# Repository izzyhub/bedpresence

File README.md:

# bedpresence

Wooohooo a new package!

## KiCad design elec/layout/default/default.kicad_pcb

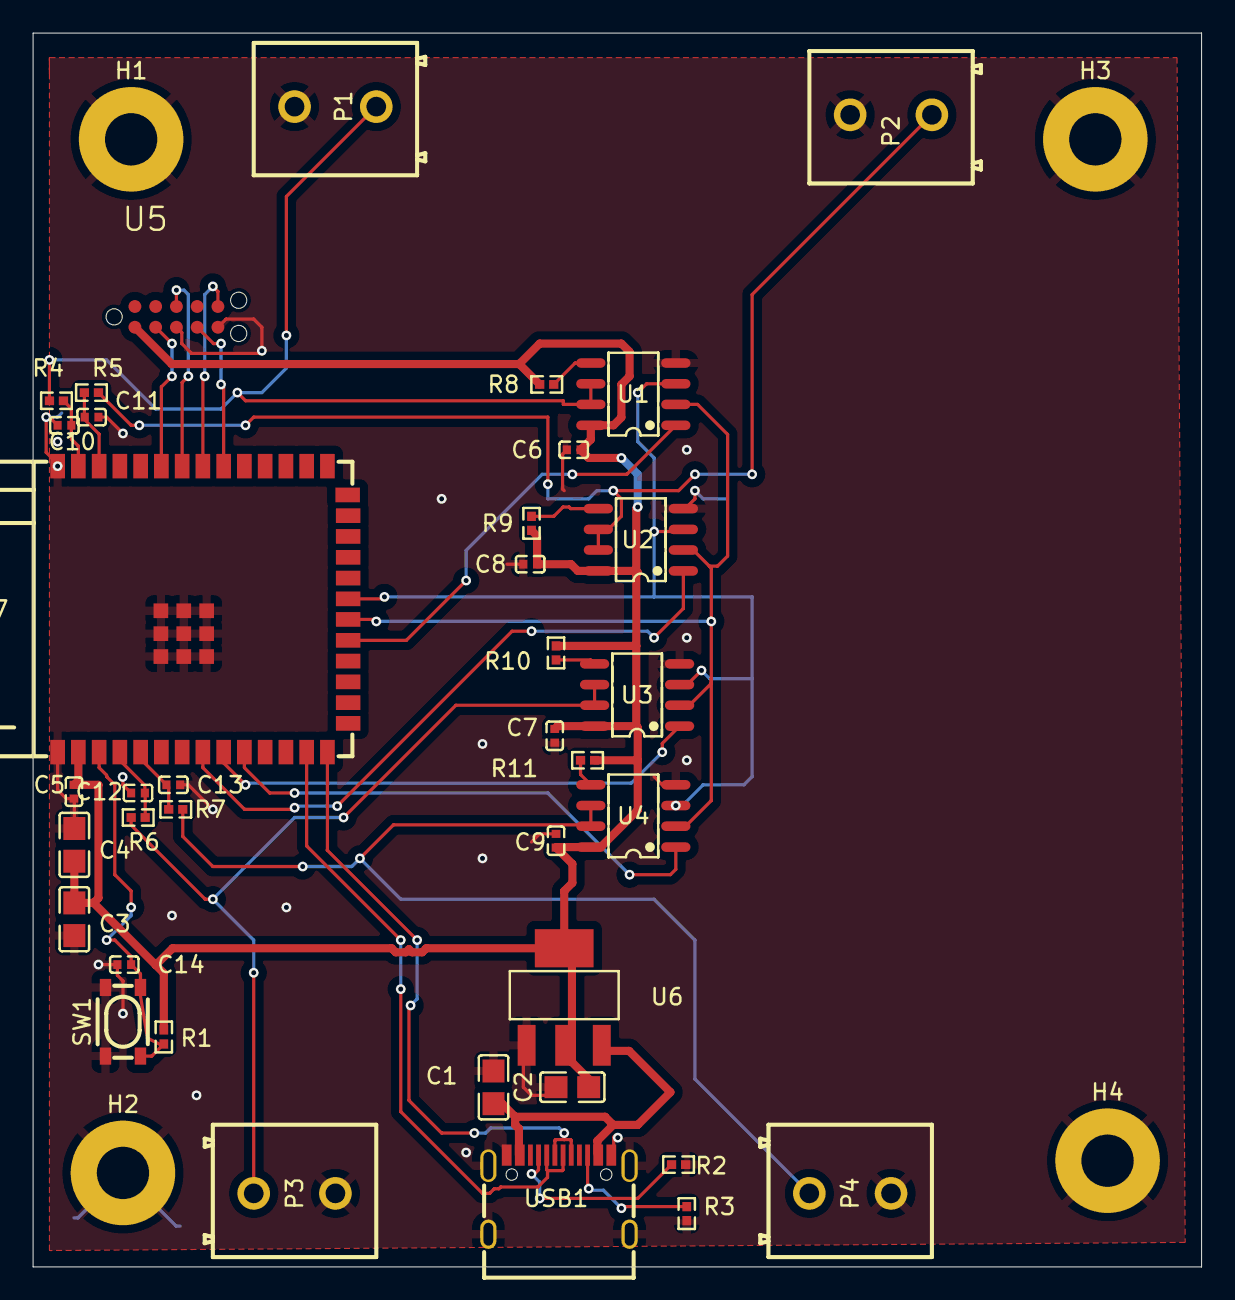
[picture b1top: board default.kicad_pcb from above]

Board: 2 copper layers, 71.5 x 75.5 mm, 42 parts (0 on the bottom side), 30 nets.

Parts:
C1, C3, C4: 10µF ±10%; C0805
C2: 22µF ±20%; C0805
C5, C6, C7, C8, C9, C10, C11, C12, C13: 100nF ±10%; C0402
C14: 1µF ±10%; C0402
H1, H2, H3, H4: MountingHole_3.2_M3_Pad
P1, P2, P3, P4: CONN-TH_2P-P5.00_CPC3703CTR
R1: 10kΩ ±1%; R0402
R2, R3: 5.1kΩ ±1%; R0402
R4, R5, R6, R7: 1kΩ ±1%; R0402
R8, R9, R10, R11: 4.02kΩ ±1%; R0402
SW1: KEY-SMD_4P-L4.2-W3.2-P2.20-LS4.6
U1, U2, U3, U4: SOIC-8_L4.9-W3.9-P1.27-LS6.0-BL
U5: TAG-CONNECT_TC2050-IDC
U6: SOT-223-3_L6.5-W3.4-P2.30-LS7.0-BR
U7: WIRELM-SMD_ESP32-S3-WROOM-1
USB1: USB-C-SMD_KH-TYPE-C-16P

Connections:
1: P1.1, R4.1, U1.6, U1.7
1-1: P2.1, R5.1, U2.6, U2.7
1-2: P3.1, R6.1, U3.6, U3.7
1-3: P4.1, R7.1, U4.6, U4.7
5: R8.2, U1.5
5-1: R9.2, U2.5
5-2: R10.2, U3.5
5-3: R11.2, U4.5
A5: R2.1, USB1.A5
B5: R3.1, USB1.B5
SI: U1.3, U2.3, U3.3, U4.3, U7.21
cs: U1.1, U7.19
digi_pot2-spi-cs: U2.1, U7.8
digi_pot3-spi-cs: U3.1, U7.9
digi_pot4-spi-cs: U4.1, U7.10
dm: U7.13, USB1.A7, USB1.B7
dp: U7.14, USB1.A6, USB1.B6
en_cap-power-hv: C14.1, R1.2, SW1.1, SW1.2, U7.3
filter_cap1-power-hv: C10.1, R4.2, U7.39
filter_cap2-power-hv: C11.1, R5.2, U7.38
filter_cap3-power-hv: C12.1, R6.2, U7.4
filter_cap4-power-hv: C13.1, R7.2, U7.5
hv: C2.1, C3.1, C4.1, C5.1, C6.1, C7.1, C8.1, C9.1, R1.1, R8.1, R9.1, R10.1, R11.1, U1.8, U2.8, U3.8, U4.8, U5.1, U6.2, U6.4, U7.2
input_cap-power-hv: C1.1, U6.3, USB1.A4, USB1.A9, USB1.B4, USB1.B9
lv: C1.2, C2.2, C3.2, C4.2, C5.2, C6.2, C7.2, C8.2, C9.2, C10.2, C11.2, C12.2, C13.2, C14.2, H1.1, H2.1, H3.1, H4.1, P1.2, P2.2, P3.2, P4.2, R2.2, R3.2, SW1.3, SW1.4, U1.4, U2.4, U3.4, U4.4, U5.3, U5.5, U6.1, U7.1, U7.40, U7.41, USB1.1, USB1.2, USB1.3, USB1.4, USB1.A1, USB1.A12, USB1.B1, USB1.B12
sck: U1.2, U2.2, U3.2, U4.2, U7.20
tck: U5.4, U7.32
tdi: U5.8, U7.34
tdo: U5.6, U7.33
tms: U5.2, U7.35

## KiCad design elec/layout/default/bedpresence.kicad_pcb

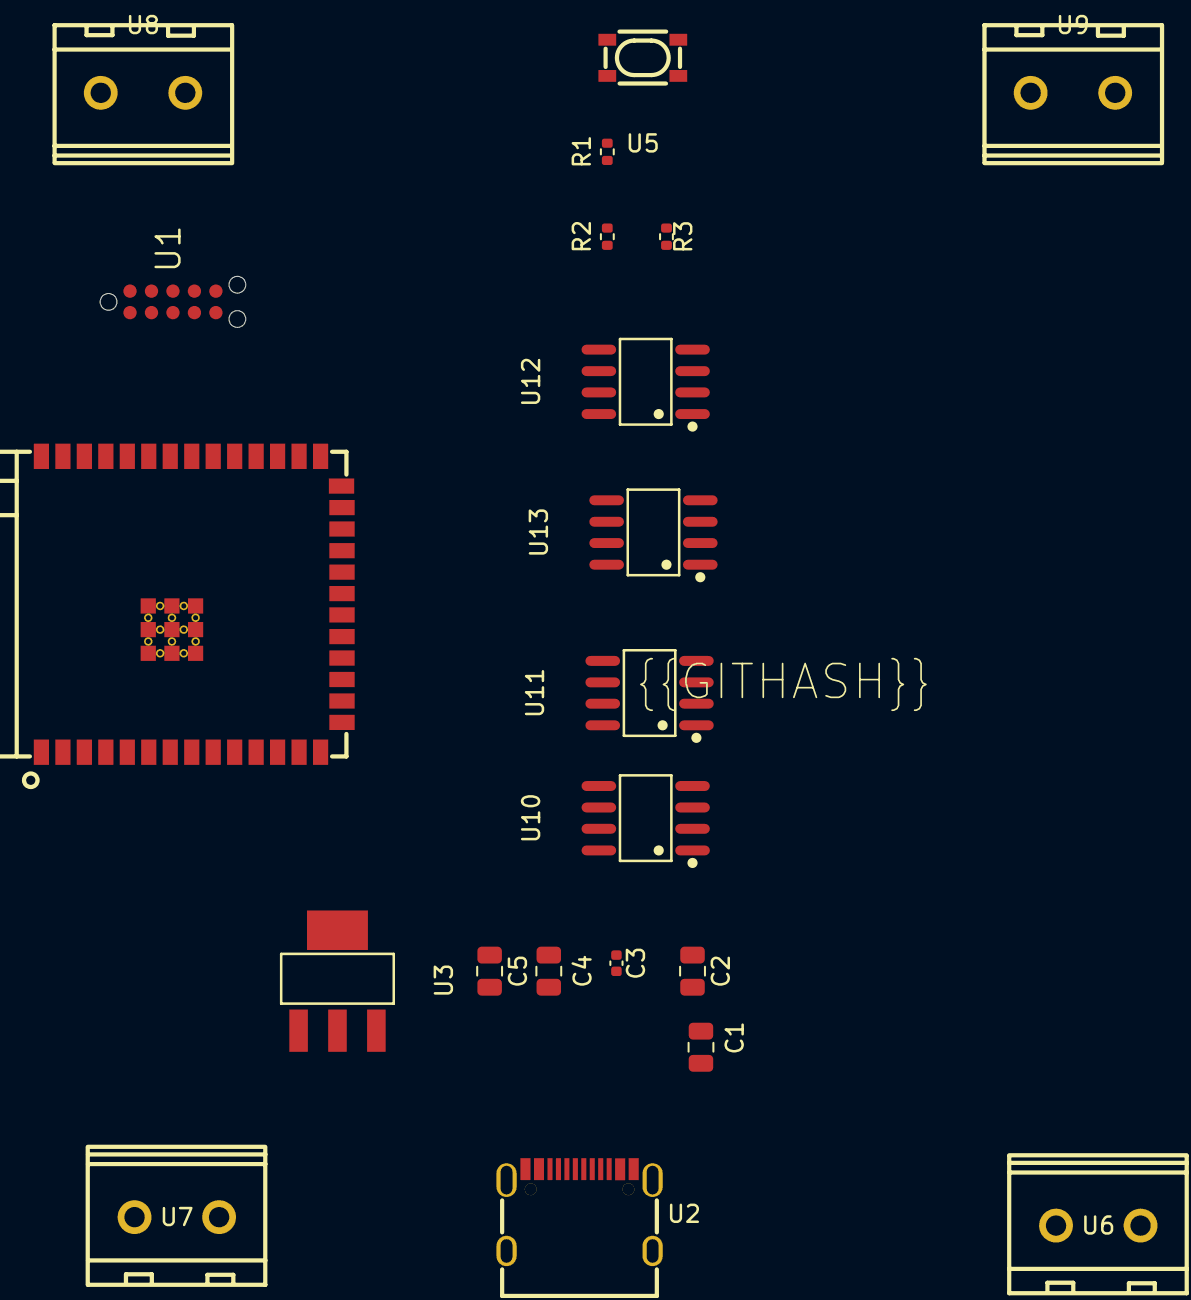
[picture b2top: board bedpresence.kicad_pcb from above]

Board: 2 copper layers, 21 parts (0 on the bottom side), 22 nets, no tracks yet.

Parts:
C1, C2, C4, C5: 25V 10uF X5R ±10% 0805 Multilayer Ceramic Capacit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; C0805
C3: 16V 100nF X7R ±10% 0402 Multilayer Ceramic Capaci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; C0402
R1, R2: 62.5mW Thick Film Resistors 50V ±100ppm/℃ ±1% 4.7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; R0402
R3: 62.5mW Thick Film Resistors 50V ±100ppm/℃ ±1% 10k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; R0402
U1: ?; TAG-CONNECT_TC2050-IDC
U2: ?; USB-C-SMD_KH-TYPE-C-16P
U3: ?; SOT-223-3_L6.5-W3.4-P2.30-LS7.0-BR
U4: ?; WIRELM-SMD_ESP32-S3-WROOM-1
U5: ?; KEY-SMD_4P-L4.2-W3.2-P2.20-LS4.6
U6, U7, U8, U9: ?; CONN-TH_2P-P5.00_CPC3703CTR
U10, U11, U12, U13: ?; SOIC-8_L4.9-W3.9-P1.27-LS6.0-BL

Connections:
cc1: R1.1, U2.A5
cc2: R2.1, U2.B5
connector1-_1: U6.1, U10.7
connector2-_1: U7.1, U11.7
connector3-_1: U8.1, U12.7
connector4-_1: U9.1, U13.7
dm: U2.A7, U2.B7, U4.13
dp: U2.A6, U2.B6, U4.14
en: R3.2, U4.3, U5.1, U5.2
gnd-1: C1.2, C2.2, C3.2, C4.2, C5.2, R1.2, R2.2, U1.3, U1.5, U2.1, U2.2, U2.3, U2.4, U2.A1, U2.A12, U2.B1, U2.B12, U3.1, U4.1, U4.40, U4.41, U5.3, U5.4, U6.2, U7.2, U8.2, U9.2, U10.4, U11.4, U12.4, U13.4
micro.ic-cs: U4.19, U10.1
micro.ic-cs-1: U4.10, U13.1
micro.ic-cs-2: U4.9, U12.1
micro.ic-cs-3: U4.8, U11.1
mosi: U4.21, U10.3, U11.3, U12.3, U13.3
sck: U4.20, U10.2, U11.2, U12.2, U13.2
tck: U1.4, U4.32
tdi: U1.8, U4.34
tdo: U1.6, U4.33
tms: U1.2, U4.35
vcc: C1.1, U1.1, U2.A4, U2.A9, U2.B4, U2.B9, U3.3
vcc-1: C2.1, C3.1, C4.1, C5.1, R3.1, U3.2, U3.4, U4.2, U10.5, U10.8, U11.5, U11.8, U12.5, U12.8, U13.5, U13.8

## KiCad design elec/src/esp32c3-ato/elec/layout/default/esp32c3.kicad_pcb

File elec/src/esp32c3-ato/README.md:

# ESP32-C3-MINI-1U-N4

📒 [Datasheet](https://www.espressif.com/sites/default/files/documentation/esp32-c3-mini-1_datasheet_en.pdf)

This repository is an [atopile](https://atopile.io/) module for the ESP32-C3-MINI-*, a system-on-chip ESP32 WiFi/BLE chip. 
- external antenna connector (ESP32-C3-MINI-1U-N4) or PCB antenna (ESP32-C3-MINI-1-N4)
- RISC­V single­core microprocessor
- 4 MB flash in chip package
- 15 GPIOs
- integrated USB controller

## 🏁 Get started
### Installation
From inside a project directory terminal: `ato install esp32c3-ato`

### Code
```ato
from "esp32c3-ato/esp32c3.ato" import ESP32C3_EXT_ANT
# - or -
from "esp32c3-ato/esp32c3.ato" import ESP32C3_PCB_ANT

from "generics/interfaces.ato" import Power
from "generics/interfaces.ato" import UART
from "generics/interfaces.ato" import USB2

module Esp:
    vdd3v3 = new Power
    uart = new UART
    usb = new USB2

    esp_ext = new ESP32C3_EXT_ANT   # external antenna connector
    esp_ext.power ~ vdd3v3
    esp_ext.uart ~ uart
    esp_ext.usb ~ usb

    # - or -
    
    esp_pcb = new ESP32C3_PCB_ANT   # PCB antenna
    esp_pcb.power ~ vdd3v3
    esp_pcb.uart ~ uart
    esp_pcb.usb ~ usb
```
*GPIO pins are available as IO0 - IO19*

## 🤔 Design Considerations
This is a minimal circuit:
- to use the USB lines to spec, you'll need to add your own resistors and capacitors per Figure 7, pg 25 of the datasheet
- there's no crystal in this design, it is required for light-sleep mode

## ⚡ Programming
The ESP32-C3 can have firmware uploaded with just a USB cable. No additional hardware is required, although this method *isn't the best approach a smooth development experience.*
### Connections
You'll need a USB breakout board or other means to access the cables and a 3.3 volt power source, not the 5 volt USB line. Tie all grounds together. 

|ESP| | USB| |3V3
|-------:|:-:|:---:|:-:|:---|
| ESP.D+ 🟨|~| 🟨 USB.D+||
| ESP.D- 🟦|~| 🟦 USB.D-||
| *ESP.VCC* 🟥|~|~|~|🟥 *3V3.VCC*|
|**ESP.GND**⬛ |~| ⬛ **USB.GND** ⬛|~|⬛ **3V3.GND**|

### Procedure
1. Reset the chip while holding IO9 LOW.
    - a reset can be accomplished by a power-cycle, or bringing the EN pin LOW then HIGH
2. Upload the firmware
3. Return IO9 to its default HIGH state
4. Power-cycle the chip to run normally

### Arduino and PlatformIO
#### Arduino
- follow [Espressif's instructions](https://docs.espressif.com/projects/arduino-esp32/en/latest/installing.html) for adding ESP32 support. 
- choose `ESP32C3 Dev Module` from the list
    - use `USBSerial` instead of `Serial` if using the same USB cable as you did for firmware upload

#### PlatformIO
```ini
[env:esp32-c3-devkitm-1]
platform = espressif32
board = esp32-c3-devkitm-1
```
*use `USBSerial` instead of `Serial` if using the same USB cable as you did for firmware upload*

## 🙏 Contributing
This design is intended to be a community best-effort at a minimal circuit combining:
- datasheet reference design
- readily available components
- modular and reusable layout

You are greatly encouraged to contribute or discuss any improvements here so that everyone may benefit. 

## License
[CERN-OHL-P v2](https:/cern.ch/cern-ohl)

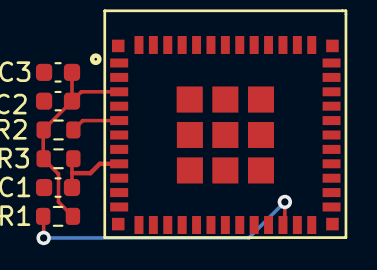
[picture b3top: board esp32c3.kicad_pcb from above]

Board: 2 copper layers, 7 parts (0 on the bottom side), 5 nets.

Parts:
C1: 50V 1uF X5R ±10% 0603 Multilayer Ceramic Capacito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; C0603
C2: 10V 10uF X5R ±10% 0603 Multilayer Ceramic Capacit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; C0603
C3: 50V 100nF X7R ±10% 0603 Multilayer Ceramic Capaci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; C0603
R1, R2, R3: 100mW Thick Film Resistors ±100ppm/℃ ±1% 10kΩ 060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; R0603
U1: WIFIM-SMD_61P-L13.2-W12.5-P0.80

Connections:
en: C1.1, R3.2, U1.8
gnd: C1.2, C2.2, C3.2, U1.1, U1.2, U1.11, U1.14, U1.36, U1.37, U1.38, U1.39, U1.40, U1.41, U1.42, U1.43, U1.44, U1.45, U1.46, U1.47, U1.48, U1.49, U1.50, U1.51, U1.52, U1.53, U1.54, U1.55, U1.56, U1.57, U1.58, U1.59, U1.60, U1.61
io2: R2.1, U1.5
io8: R1.1, U1.22
vcc: C2.1, C3.1, R1.2, R2.2, R3.1, U1.3

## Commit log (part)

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2025-03-01 Configure project
2025-03-01 Basic PCB for bed presence connector and FSR connectors.
2025-03-02 Some kicad fiddling. Fix missing models. Fix their orientations etc.
2025-03-02 Start work on using digital potentiometers instead of more manual stuff.
    This will let me do calibration in software instead of manually with a screw.
    Mostly saving this so I can work on this on a different machine for a bit.
2025-03-05 Switch to digital potentiometers.
